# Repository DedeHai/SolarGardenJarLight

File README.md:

# Solar Garden Jar Light
A solar powered LED light controlled by an Arduino. It is designed to fit inside most glass jars lighting up your garden or back yard in beatuiful colors. 
The Arduino is connected to an accelerometer to switch the light on and off and to change the color by tilting it. It was designed with easy assembly in mind to be sold as a DIY kit at [Fablab Winti](www.fablabwinti.ch). The voltage regulator as well as the power LED are removed from the Arduino to make it low power consumption consuming only 120µA on average when switched off, making the 500mAh battery last up to half a year when kept in the dark. The solar cell voltage is used to detect low light conditions at dawn and the light does automatically switch on for a few hours if the battery is fully charged. The threshold levels can be adjusted easily in the software.

More information available at https://bashtelorofscience.wordpress.com/ 

License:
Software source code is GNU GPL V3 licensed
Hardware under Creative Commons 4.0 license: CC-BY-NC-SA

# Software
The PCB was designed in **eagle** version 7.5.0. The firmware project was created using **Arduino IDE**.

# Fotos

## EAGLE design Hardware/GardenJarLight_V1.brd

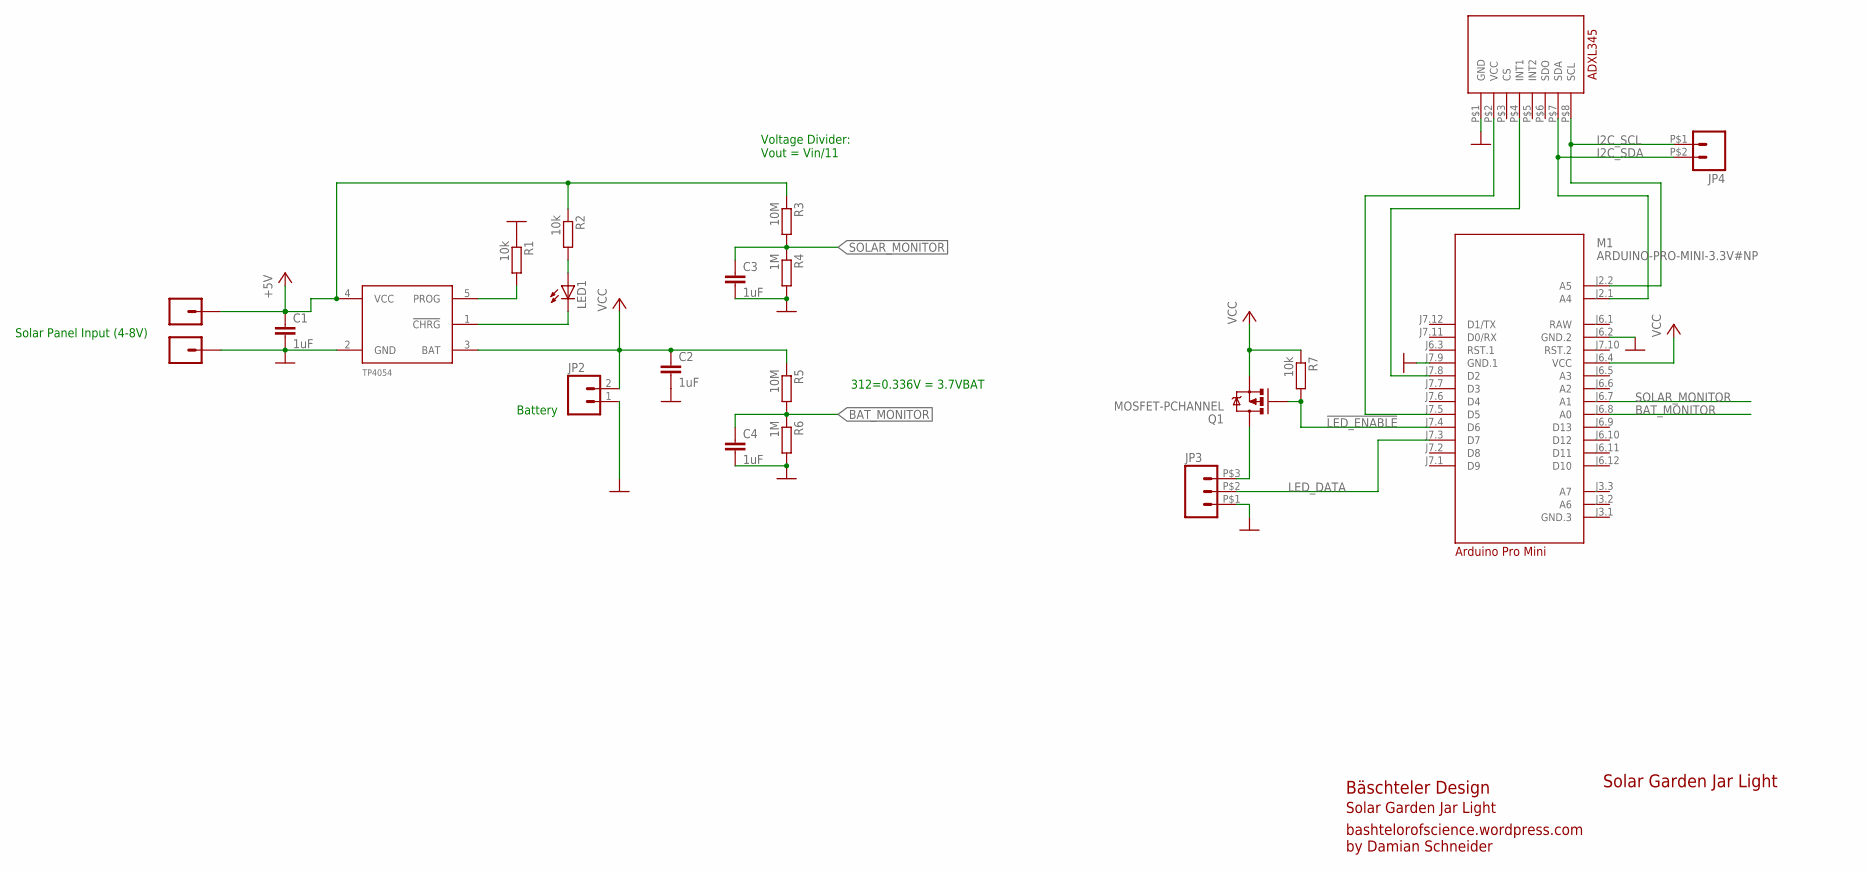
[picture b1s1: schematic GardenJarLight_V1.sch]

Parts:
C1, C2, C3, C4: 1uF; C0805
IC1: TP4054_LIPO_CHARGER; SOT23-5
JP1, JP5: M01PTH; 1X01
JP2: M021X02_NO_SILK; 1X02_NO_SILK
JP3: M03SMD_LONG; SMD_HEADER_3P_LONG
JP4: M02; SMD_HEADER_2P
LED1: LEDCHIPLED_0805; CHIPLED_0805
M1: ARDUINO-PRO-MINI-3.3V#NP; ARDUINO-PRO-MINI#NP
Q1: MOSFET-PCHANNEL; SOT23-3
R1, R2, R7: 10k; R0805
R3, R5: 10M; R0805
R4, R6: 1M; R0805
U$1: ADXL345

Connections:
!LED_ENABLE: M1.J7.4 (D6), Q1.1 (G), R7.2
+5V: C1.1, IC1.4 (VCC), JP1.1, R2.1, R3.1
BAT_MONITOR: C4.1, M1.J6.8 (A0), R5.2, R6.1
GND: C1.2, C2.2, C3.2, C4.2, IC1.2 (GND), JP2.1, JP3.P$1 (1), JP5.1, M1.J6.2 (GND.2), M1.J7.9 (GND.1), R1.1, R4.2, R6.2, U$1.P$1 (GND)
I2C_SCL: JP4.P$1 (1), M1.J2.2 (A5), U$1.P$8 (SCL)
I2C_SDA: JP4.P$2 (2), M1.J2.1 (A4), U$1.P$7 (SDA)
LED_DATA: JP3.P$2 (2), M1.J7.3 (D7)
unnamed: JP3.P$3 (3), Q1.3 (D)
unnamed: IC1.1 (!CHRG), LED1.C
unnamed: IC1.5 (PROG), R1.2
unnamed: M1.J7.8 (D2), U$1.P$4 (INT1)
unnamed: M1.J7.5 (D5), U$1.P$2 (VCC)
unnamed: LED1.A, R2.2
RAW: M1.J6.1 (RAW)
SOLAR_MONITOR: C3.1, M1.J6.7 (A1), R3.2, R4.1
VCC: C2.1, IC1.3 (BAT), JP2.2, M1.J6.4 (VCC), Q1.2 (S), R5.1, R7.1

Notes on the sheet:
Battery
Solar Panel Input (4-8V)
312=0.336V = 3.7VBAT
Voltage Divider: Vout = Vin/11
Bäschteler Design
bashtelorofscience.wordpress.com by Damian Schneider
Solar Garden Jar Light
Arduino Pro Mini

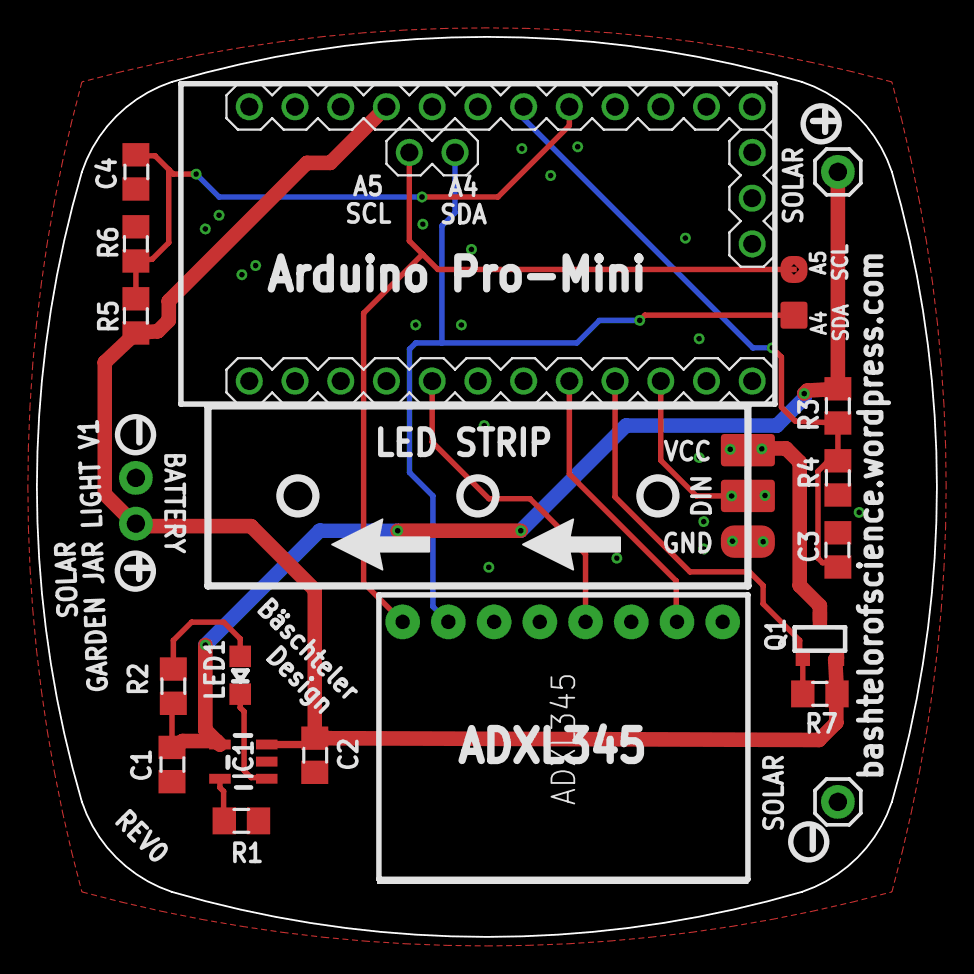
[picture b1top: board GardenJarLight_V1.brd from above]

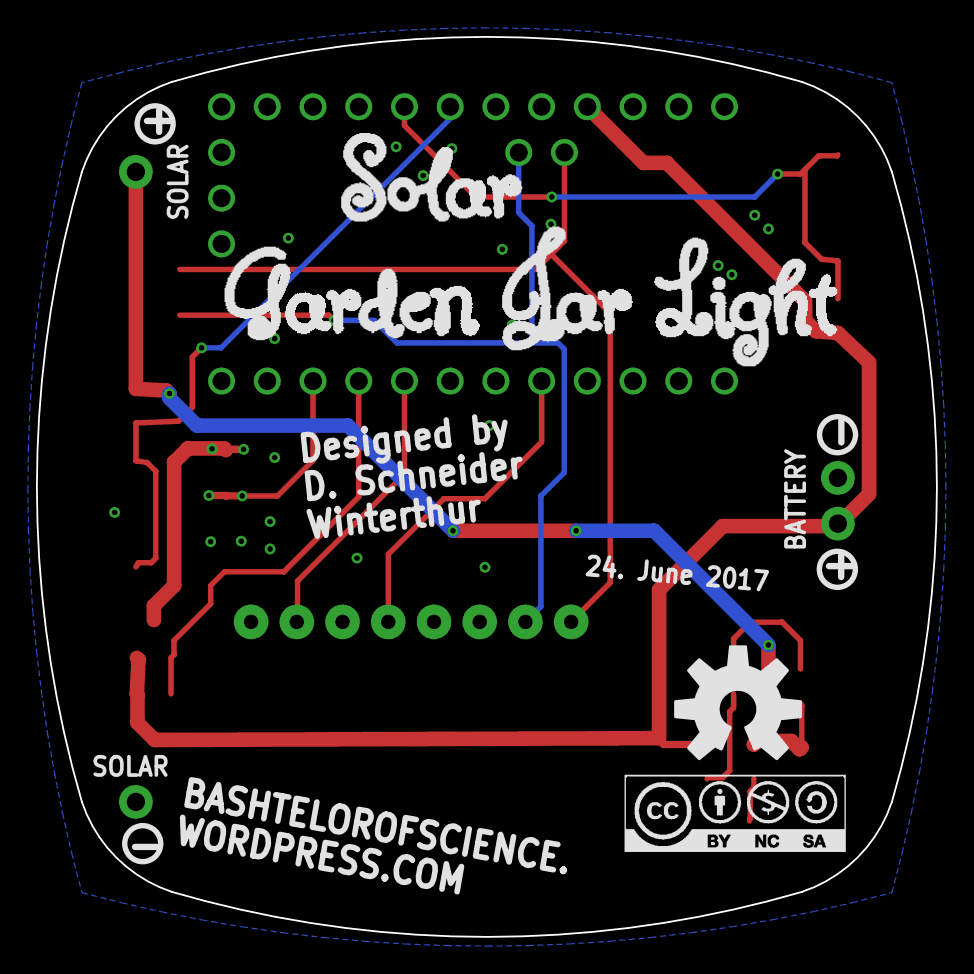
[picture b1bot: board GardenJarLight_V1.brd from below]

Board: 2 copper layers, 50.0 x 50.0 mm, 23 parts (2 on the bottom side), 15 nets.

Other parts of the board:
U$4: CC-BY-NC-SA
U$33: OSHW-LOGO-L

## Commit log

2017-07-11 fixed image
2017-07-11 Auto switchoff bugfix
    automatic switchoff happened way too soon, found a bug in the time
    calculation
2017-07-11 fixed bug in timing
2017-07-12 more timing bugfixes & adjustments
2017-07-15 small update
    added brightness and saturation reset upon double tap, changed auto-off
    time to 5 hours
2017-07-20 BUGFIX: auto-on works now
    auto on worked only once, the minutecounter was not reset. also adjusted
    some constants
2017-07-22 Bauanleitung hinzugefügt
2017-07-23 increased watchtdog timeout
    bootloader kept resetting at 250ms
2017-07-23 updated Bauanleitung
2017-07-23 updated yet again
2017-07-26 typo fixed
2017-07-29 updated schematic
2017-08-01 changed constants once again
2017-08-01 adding bauanleitung source file
2017-08-01 Diverse Schreibfehler behoben, BOM aktualisiert
2017-08-01 bauanleitung update, bom und typos
2017-08-01 updated silkscreen
2017-08-05 bugfix & added daytime shutdown
    fixed a bug where after double tap it does not go to color changing mode
    but to brightness chaning mode.
    Added a feature: during broad daylight it shuts down automatically after
    one minute or so
2017-09-10 added auto off during daylight
    and some bugfixes
2017-11-15 watchdog bug fixed
    (probably) found and fixed the bug where the watchdog was able to reset
    the system twice in a row, causing the bootloader to get stuck in an
    infinite loop.
2019-01-07 some tweaking or parameters and bugfixes
2019-05-03 Added color randomisation and auto adjusting brightness
    also did some more testing, found a correctly working version for
    infinite loops
    also upon auto-on the color is chosen randomly
    the brightness is chosen according to power left in the battery, if
    battery did not charge much, brightness is reduced so lanterns should
    turn on most days even in the winter.

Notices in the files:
README.md:
License: CC BY-NC-SA 4.0
parts and their libraries:
diy-modules: Released under the Creative Commons Attribution 4.0 International License: http://creativecommons.org/licenses/by/4.0
SparkFun-DiscreteSemi: Licensing: Creative Commons ShareAlike 4.0 International - https://creativecommons.org/licenses/by-sa/4.0
